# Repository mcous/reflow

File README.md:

# reflow

Heater controller with thermocouple feedback to control any AC heating appliance. It was originally developed to turn a toaster oven into a solder reflow oven, but it'll control anything that runs on AC and gets hot.

## hardware v0.1

The current board contains an AVR ATMega328P microcontroller, a Sharp S212S01 solid-state relay, and an Analog Devices AD8495 K-type thermocouple amplifier. It has a temperature precision of about 0.5 degrees C and is accurate to about +/- 2 degrees C. It also has start, stop, and mode buttons; a rotary encoder for temperature settings; and a four-digit seven-segment display for showing temperature in C or F. 

The schematic and PCB layout files were created in [KiCad](http://www.kicad-pcb.org) and live the in `pcb` directory.

## firmware v0.1.1

The current firmware has two basic modes: hit and hold. Hit mode takes the temperature up to the set point and then shuts off, while hold mode attempts to hold the temperature at the set-point by turning the heat on when the temperature is below the set point, and off when it's above. This is not PID. It can also display the temperature in either Celsius or Fahrenheit.

The firmware is written in C++ and compiled on OS X using the latest [CrossPack for AVR](http://www.obdev.at/products/crosspack/index.html) and lives in the `firmware` directory. It'll probably compile fine on Linux; no idea about Windows, though.

## operation

* To switch temperature units, hold the set wheel down (it's also a button) until you see an F after the temperature (Fahrenheit) or a number with a decimal point (Celsius)
* To switch modes between hit and hold, press and release the set wheel button; the display will show either "hit" or "hold" for whatever mode has been selected
* To select a set point, turn the set wheel until the display shows your desired temperature
* Press the start button to start heating; the red light will go out and the green light will illuminate
	* In hit mode, once the temperature is hit, the heating will stop and the green light will go out, replaced by the red light
	* In hold mode, the program will not stop unless you tell it to
* Press the stop button to stop heating; the green light will go out and the red light will illuminate
* Whenever the relay is closed (i.e. heat is on) the red LED labeled "HOT" will illuminate

## things this board has been used for

* reflow toaster oven (in hit mode)
* sous vide slow-cooker (in hold mode)

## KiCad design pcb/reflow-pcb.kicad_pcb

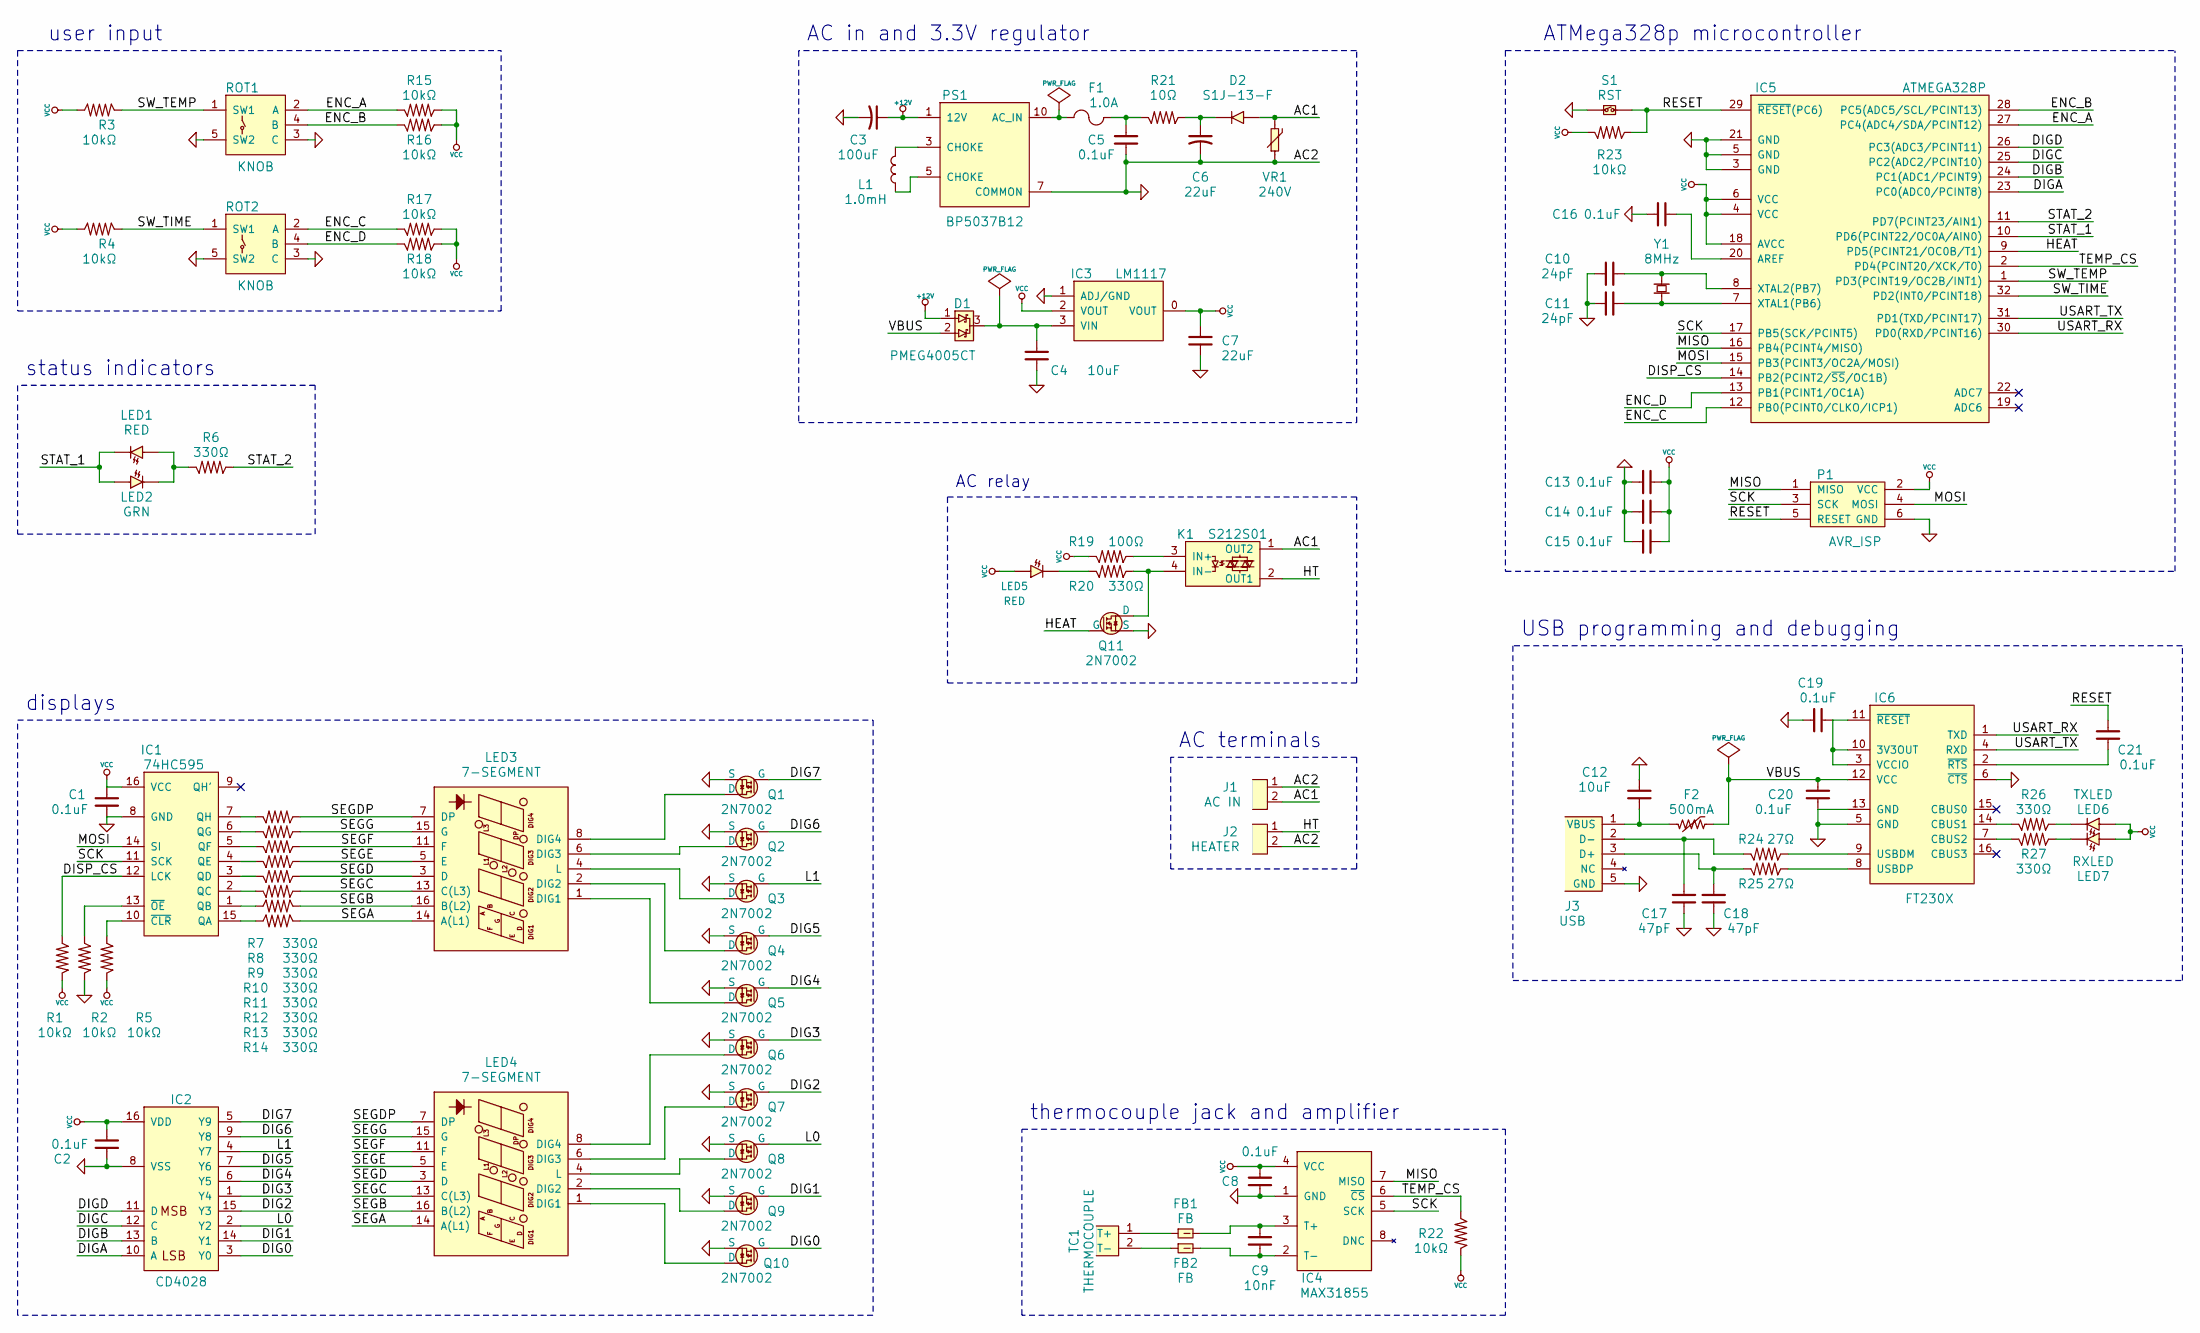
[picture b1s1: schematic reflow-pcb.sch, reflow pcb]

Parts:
C1, C2, C21: 0.1uF
C3: 100uF; Manuf. Part EEE-FT1E101AP
C4: 10uF
C5: 0.1uF; Manuf. Part CL31B104KEHSFNE
C6: 22uF; Manuf. Part EEU-EE2E220
C7: 22uF
C8, C13, C14, C15, C19, C20: 0.1uF; 0603(1608m)
C9: 10nF; 0603(1608m)
C10, C11: 24pF
C12: 10uF
C16: 0.1uF
C17, C18: 47pF; 0603(1608m)
D1: PMEG4005CT
D2: S1J-13-F; Manuf. Part S1J-13-F
F1: 1.0A; Manuf. Part C1Q 1
F2: 500mA; 1206(3216m); Part 0ZCJ0050FF2G
FB1, FB2: FB
IC1: 74HC595
IC2: CD4028
IC3: LM1117; Part AZ1117CH-3.3TRG1
IC4: MAX31855; Part MAX31855KASA+
IC5: ATMEGA328P; TQFP32_7mm; Part ATMEGA328P-AU
IC6: FT230X; SSOP16; Part FT230XS-R
J1: AC IN
J2: HEATER; 2-PIN_SCREW-TERM_P200MIL; Part OSTTC022162
J3: USB; MICROUSB_sm; Part 10118192-0001LF
K1: S212S01; SHARP_SIP_SSR; Part S212S01F
L1: 1.0mH; Manuf. Part SRR1260-102K
LED1, LED5: RED; LED-5mm
LED2: GRN; LED-5mm
LED3, LED4: 7-SEGMENT; Manuf. Part LTC-4727JR
LED6: TXLED; 0603(1608m)_led
LED7: RXLED; 0603(1608m)_led
P1: AVR_ISP; 2x3-array
PS1: BP5037B12; Manuf. Part BP5037B12
Q1, Q2, Q3, Q4, Q5, Q6, Q7, Q8, Q9, Q10, Q11: 2N7002; Manuf. Part 2N7002P,215
R1, R22, R23: 10kΩ
R2, R5: 10kΩ
R3, R4, R15, R16, R17, R18: 10kΩ; 0603(1608m)
R6: 330Ω
R7, R8, R9, R10, R11, R12, R13, R14, R20, R26, R27: 330Ω; 0603(1608m)
R19: 100Ω; 0603(1608m)
R21: 10Ω; Manuf. Part RC1206FR-0710RL
R24, R25: 27Ω; 0603(1608m)
ROT1, ROT2: KNOB; SF_ROTARY-ENCODER; Part RE130F-41-175F-12P
S1: RST
TC1: THERMOCOUPLE; THERMOCOUPLE_MINI_PCC-SMP; Part PCC-SMP-K
VR1: 240V; Manuf. Part MOV-14D241K
Y1: 8MHz

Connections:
+12V: C3.1, D1.1 (A1), PS1.1 (12V)
/AC1: D2.2 (A), J1.2, K1.1 (OUT2), VR1.2
/DIG0: IC2.3 (Y0), Q10.1 (G)
/DIG1: IC2.14 (Y1), Q9.1 (G)
/DIG2: IC2.15 (Y3), Q7.1 (G)
/DIG3: IC2.1 (Y4), Q6.1 (G)
/DIG4: IC2.6 (Y5), Q5.1 (G)
/DIG5: IC2.7 (Y6), Q4.1 (G)
/DIG6: IC2.9 (Y8), Q2.1 (G)
/DIG7: IC2.5 (Y9), Q1.1 (G)
/DIGA: IC2.10 (A), IC5.23 (PC0(ADC0/PCINT8))
/DIGB: IC2.13 (B), IC5.24 (PC1(ADC1/PCINT9))
/DIGC: IC2.12 (C), IC5.25 (PC2(ADC2/PCINT10))
/DIGD: IC2.11 (D), IC5.26 (PC3(ADC3/PCINT11))
/DISP_CS: IC1.12 (LCK), IC5.14 (PB2(PCINT2/~SS~/OC1B)), R1.2
/ENC_A: IC5.27 (PC4(ADC4/SDA/PCINT12)), R15.1, ROT1.2 (A)
/ENC_B: IC5.28 (PC5(ADC5/SCL/PCINT13)), R16.1, ROT1.4 (B)
/ENC_C: IC5.12 (PB0(PCINT0/CLKO/ICP1)), R17.1, ROT2.2 (A)
/ENC_D: IC5.13 (PB1(PCINT1/OC1A)), R18.1, ROT2.4 (B)
/HEAT: IC5.9 (PD5(PCINT21/OC0B/T1)), Q11.1 (G)
/HT: J2.1, K1.2 (OUT1)
/L0: IC2.2 (Y2), Q8.1 (G)
/L1: IC2.4 (Y7), Q3.1 (G)
/MISO: IC4.7 (MISO), IC5.16 (PB4(PCINT4/MISO)), P1.1 (MISO)
/MOSI: IC1.14 (SI), IC5.15 (PB3(PCINT3/OC2A/MOSI)), P1.4 (MOSI)
/RESET: C21.2, IC5.29 (~RESET~(PC6)), P1.5 (RESET), R23.2, S1.2
/SCK: IC1.11 (SCK), IC4.5 (SCK), IC5.17 (PB5(SCK/PCINT5)), P1.3 (SCK)
/SEGA: LED3.14 (A(L1)), LED4.14 (A(L1)), R14.1
/SEGB: LED3.16 (B(L2)), LED4.16 (B(L2)), R13.1
/SEGC: LED3.13 (C(L3)), LED4.13 (C(L3)), R12.1
/SEGD: LED3.3 (D), LED4.3 (D), R11.1
/SEGDP: LED3.7 (DP), LED4.7 (DP), R7.1
/SEGE: LED3.5 (E), LED4.5 (E), R10.1
/SEGF: LED3.11 (F), LED4.11 (F), R9.1
/SEGG: LED3.15 (G), LED4.15 (G), R8.1
/STAT_1: IC5.10 (PD6(PCINT22/OC0A/AIN0)), LED1.1 (C), LED2.2 (A)
/STAT_2: IC5.11 (PD7(PCINT23/AIN1)), R6.2
/SW_TEMP: IC5.1 (PD3(PCINT19/OC2B/INT1)), R3.1, ROT1.1 (SW1)
/SW_TIME: IC5.32 (PD2(INT0/PCINT18)), R4.1, ROT2.1 (SW1)
/TEMP_CS: IC4.6 (~CS~), IC5.2 (PD4(PCINT20/XCK/T0)), R22.2
/USART_RX: IC5.30 (PD0(RXD/PCINT16)), IC6.1 (TXD)
/USART_TX: IC5.31 (PD1(TXD/PCINT17)), IC6.4 (RXD)
/VBUS: C20.2, D1.2 (A2), F2.1, IC6.12 (VCC)
GND: C1.1, C2.2, C3.2, C4.1, C5.1, C6.2, C7.1, C8.1, C10.1, C11.1, C12.1, C13.1, C14.1, C15.1, C16.1, C17.1, C18.1, C19.1, C20.1, IC1.8 (GND), IC2.8 (VSS), IC3.1 (ADJ/GND), IC4.1 (GND), IC5.3 (GND), IC5.5 (GND), IC5.21 (GND), IC6.5 (GND), IC6.6 (~CTS~), IC6.13 (GND), J1.1, J2.2, J3.5 (GND), P1.6 (GND), PS1.7 (COMMON), Q1.2 (S), Q2.2 (S), Q3.2 (S), Q4.2 (S), Q5.2 (S), Q6.2 (S), Q7.2 (S), Q8.2 (S), Q9.2 (S), Q10.2 (S), Q11.2 (S), R2.1, ROT1.3 (C), ROT1.5 (SW2), ROT2.3 (C), ROT2.5 (SW2), S1.1, VR1.1
unnamed: C4.2, D1.3 (CC), IC3.3 (VIN)
unnamed: C5.2, F1.2, R21.1
unnamed: C6.1, D2.1 (C), R21.2
unnamed: C9.1, FB2.2, IC4.2 (T-)
unnamed: C9.2, FB1.2, IC4.3 (T+)
unnamed: C10.2, IC5.8 (XTAL2(PB7)), Y1.2
unnamed: C11.2, IC5.7 (XTAL1(PB6)), Y1.1
unnamed: C12.2, F2.2, J3.1 (VBUS)
unnamed: C16.2, IC5.20 (AREF)
unnamed: C17.2, J3.2 (D-), R24.1
unnamed: C18.2, J3.3 (D+), R25.1
unnamed: C19.2, IC6.3 (VCCIO), IC6.10 (3V3OUT), IC6.11 (~RESET~)
unnamed: C21.1, IC6.2 (~RTS~)
unnamed: F1.1, PS1.10 (AC_IN)
unnamed: FB1.1, TC1.1 (T+)
unnamed: FB2.1, TC1.2 (T-)
unnamed: IC1.1 (QB), R13.2
unnamed: IC1.2 (QC), R12.2
unnamed: IC1.3 (QD), R11.2
unnamed: IC1.4 (QE), R10.2
unnamed: IC1.5 (QF), R9.2
unnamed: IC1.6 (QG), R8.2
unnamed: IC1.7 (QH), R7.2
unnamed: IC1.10 (~CLR~), R5.2
unnamed: IC1.13 (~OE~), R2.2
unnamed: IC1.15 (QA), R14.2
unnamed: IC6.7 (CBUS2), R27.1
unnamed: IC6.8 (USBDP), R25.2
unnamed: IC6.9 (USBDM), R24.2
unnamed: IC6.14 (CBUS1), R26.1
unnamed: K1.3 (IN+), R19.2
unnamed: K1.4 (IN-), Q11.3 (D), R20.2
unnamed: L1.1, PS1.5 (CHOKE)
unnamed: L1.2, PS1.3 (CHOKE)
unnamed: LED1.2 (A), LED2.1 (C), R6.1
unnamed: LED3.1 (DIG1), Q5.3 (D)
unnamed: LED3.2 (DIG2), Q4.3 (D)
unnamed: LED3.4 (L), Q3.3 (D)
unnamed: LED3.6 (DIG3), Q2.3 (D)
unnamed: LED3.8 (DIG4), Q1.3 (D)
unnamed: LED4.1 (DIG1), Q10.3 (D)
unnamed: LED4.2 (DIG2), Q9.3 (D)
unnamed: LED4.4 (L), Q8.3 (D)
unnamed: LED4.6 (DIG3), Q7.3 (D)
unnamed: LED4.8 (DIG4), Q6.3 (D)
unnamed: LED5.1 (C), R20.1
unnamed: LED6.1 (C), R26.2
unnamed: LED7.1 (C), R27.2
VCC: C1.2, C2.1, C7.2, C8.2, C13.2, C14.2, C15.2, IC1.16 (VCC), IC2.16 (VDD), IC3.0 (VOUT), IC3.2 (VOUT), IC4.4 (VCC), IC5.4 (VCC), IC5.6 (VCC), IC5.18 (AVCC), LED5.2 (A), LED6.2 (A), LED7.2 (A), P1.2 (VCC), R1.1, R3.2, R4.2, R5.1, R15.2, R16.2, R17.2, R18.2, R19.1, R22.1, R23.1

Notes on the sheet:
status indicators
user input
displays
AC relay
thermocouple jack and amplifier
USB programming and debugging
ATMega328p microcontroller
AC terminals
AC in and 3.3V regulator

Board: 2 copper layers, 91 parts (1 on the bottom side), 93 nets, no tracks yet.

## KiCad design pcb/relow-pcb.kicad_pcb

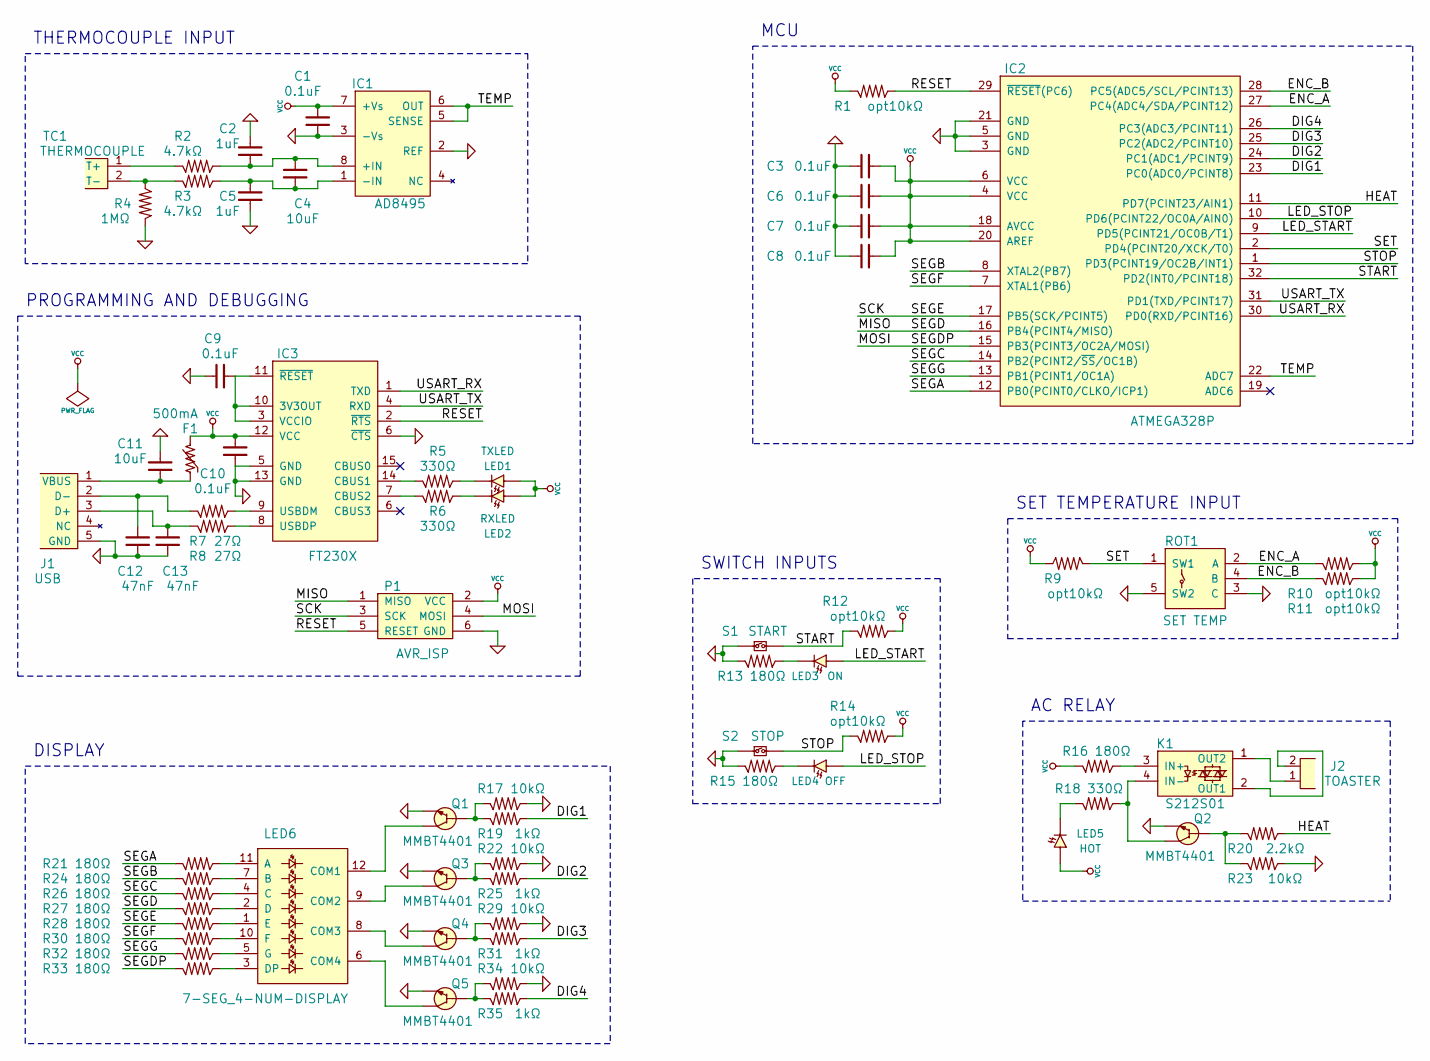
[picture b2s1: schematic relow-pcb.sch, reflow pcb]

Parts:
C1, C3, C6, C7, C8, C9, C10: 0.1uF; 0603(1608m)
C2, C5: 1uF; 0603(1608m)
C4, C11: 10uF; 0603(1608m)
C12, C13: 47nF; 0603(1608m)
F1: 500mA; 1206(3216m); Part 0ZCJ0050FF2G
IC1: AD8495; MSOP8; Part AD8495ARMZ
IC2: ATMEGA328P; TQFP32_7mm; Part ATMEGA328P-AU
IC3: FT230X; SSOP16; Part FT230XS-R
J1: USB; MICROUSB_sm; Part 10118192-0001LF
J2: TOASTER; 2-PIN_SCREW-TERM_P200MIL; Part OSTTC022162
K1: S212S01; SHARP_SIP_SSR; Part S212S01F
LED1: TXLED; 0603(1608m)_led
LED2: RXLED; 0603(1608m)_led
LED3: ON; LED-5mm
LED4: OFF; LED-5mm
LED5: HOT; LED-5mm
LED6: 7-SEG_4-NUM-DISPLAY; SF_4-DIGIT_7-SEGMENT_CC; Part COM-11405
P1: AVR_ISP; 2x3-array
Q1, Q2, Q3, Q4, Q5: MMBT4401; SOT23; Part MMBT4401LT1G
R1, R9, R10, R11, R12, R14: opt10kΩ; 0603(1608m)
R2, R3: 4.7kΩ; 0603(1608m)
R4: 1MΩ; 0603(1608m)
R5, R6, R18: 330Ω; 0603(1608m)
R7, R8: 27Ω; 0603(1608m)
R13, R15, R16, R21, R24, R26, R27, R28, R30, R32, R33: 180Ω; 0603(1608m)
R17, R22, R23, R29, R34: 10kΩ; 0603(1608m)
R19, R25, R31, R35: 1kΩ; 0603(1608m)
R20: 2.2kΩ; 0603(1608m)
ROT1: SET TEMP; SF_ROTARY-ENCODER; Part RE130F-41-175F-12P
S1: START; SPST_4-pin-thru
S2: STOP; SPST_4-pin-thru
TC1: THERMOCOUPLE; THERMOCOUPLE_MINI_PCC-SMP; Part PCC-SMP-K

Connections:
/DIG1: IC2.23 (PC0(ADC0/PCINT8)), R19.2
/DIG2: IC2.24 (PC1(ADC1/PCINT9)), R25.2
/DIG3: IC2.25 (PC2(ADC2/PCINT10)), R31.2
/DIG4: IC2.26 (PC3(ADC3/PCINT11)), R35.2
/ENC_A: IC2.27 (PC4(ADC4/SDA/PCINT12)), R10.1, ROT1.2 (A)
/ENC_B: IC2.28 (PC5(ADC5/SCL/PCINT13)), R11.1, ROT1.4 (B)
/HEAT: IC2.11 (PD7(PCINT23/AIN1)), R20.2
/LED_START: IC2.9 (PD5(PCINT21/OC0B/T1)), LED3.2 (A)
/LED_STOP: IC2.10 (PD6(PCINT22/OC0A/AIN0)), LED4.2 (A)
/MISO: IC2.16 (PB4(PCINT4/MISO)), P1.1 (MISO), R27.1
/MOSI: IC2.15 (PB3(PCINT3/OC2A/MOSI)), P1.4 (MOSI), R33.1
/RESET: IC2.29 (~RESET~(PC6)), IC3.2 (~RTS~), P1.5 (RESET), R1.2
/SCK: IC2.17 (PB5(SCK/PCINT5)), P1.3 (SCK), R28.1
/SEGA: IC2.12 (PB0(PCINT0/CLKO/ICP1)), R21.1
/SEGB: IC2.8 (XTAL2(PB7)), R24.1
/SEGC: IC2.14 (PB2(PCINT2/~SS~/OC1B)), R26.1
/SEGF: IC2.7 (XTAL1(PB6)), R30.1
/SEGG: IC2.13 (PB1(PCINT1/OC1A)), R32.1
/SET: IC2.2 (PD4(PCINT20/XCK/T0)), R9.1, ROT1.1 (SW1)
/START: IC2.32 (PD2(INT0/PCINT18)), R12.1, S1.2
/STOP: IC2.1 (PD3(PCINT19/OC2B/INT1)), R14.1, S2.2
/TEMP: IC1.5 (SENSE), IC1.6 (OUT), IC2.22 (ADC7)
/USART_RX: IC2.30 (PD0(RXD/PCINT16)), IC3.1 (TXD)
/USART_TX: IC2.31 (PD1(TXD/PCINT17)), IC3.4 (RXD)
GND: C1.1, C2.2, C3.1, C5.1, C6.1, C7.1, C8.1, C9.1, C10.1, C11.2, C12.1, C13.1, IC1.2 (REF), IC1.3 (-Vs), IC2.3 (GND), IC2.5 (GND), IC2.21 (GND), IC3.5 (GND), IC3.6 (CBUS3), IC3.13 (GND), J1.5 (GND), P1.6 (GND), Q1.2 (E), Q2.2 (E), Q3.2 (E), Q4.2 (E), Q5.2 (E), R4.1, R13.1, R15.1, R17.2, R22.2, R23.2, R29.2, R34.2, ROT1.3 (C), ROT1.5 (SW2), S1.1, S2.1; also elsewhere on the board
unnamed: LED6.11 (A), R21.2
unnamed: LED3.1 (C), R13.2
unnamed: LED4.1 (C), R15.2
unnamed: LED6.7 (B), R24.2
unnamed: LED6.4 (C), R26.2
unnamed: LED6.2 (D), R27.2
unnamed: LED6.1 (E), R28.2
unnamed: LED6.10 (F), R30.2
unnamed: LED6.5 (G), R32.2
unnamed: LED6.3 (DP), R33.2
unnamed: Q1.1 (B), R17.1, R19.1
unnamed: K1.3 (IN+), R16.2
unnamed: Q4.1 (B), R29.1, R31.1
unnamed: Q5.1 (B), R34.1, R35.1
unnamed: LED6.12 (COM1), Q1.3 (C)
unnamed: LED6.9 (COM2), Q3.3 (C)
unnamed: Q3.1 (B), R22.1, R25.1
unnamed: IC3.14 (CBUS1), R5.1
unnamed: IC3.7 (CBUS2), R6.1
unnamed: LED2.1 (C), R6.2
unnamed: IC3.8 (USBDP), R8.2
unnamed: C13.2, J1.3 (D+), R8.1
unnamed: LED1.1 (C), R5.2
unnamed: R2.1, TC1.1 (T+)
unnamed: K1.4 (IN-), Q2.3 (C), R18.2
unnamed: IC3.9 (USBDM), R7.2
unnamed: C9.2, IC3.3 (VCCIO), IC3.10 (3V3OUT), IC3.11 (~RESET~)
unnamed: J2.2, K1.2 (OUT1)
unnamed: LED5.1 (C), R18.1
unnamed: J2.1, K1.1 (OUT2)
unnamed: C12.2, J1.2 (D-), R7.1
unnamed: Q2.1 (B), R20.1, R23.1
unnamed: LED6.8 (COM3), Q4.3 (C)
unnamed: LED6.6 (COM4), Q5.3 (C)
unnamed: C2.1, C4.2, IC1.8 (+IN), R2.2
unnamed: R3.1, R4.2, TC1.2 (T-)
unnamed: C4.1, C5.2, IC1.1 (-IN), R3.2
unnamed: C11.1, F1.1, J1.1 (VBUS)
VCC: C1.2, C3.2, C6.2, C7.2, C8.2, C10.2, F1.2, IC1.7 (+Vs), IC2.4 (VCC), IC2.6 (VCC), IC2.18 (AVCC), IC2.20 (AREF), IC3.12 (VCC), LED1.2 (A), LED2.2 (A), LED5.2 (A), P1.2 (VCC), R1.1, R9.2, R10.2, R11.2, R12.2, R14.2, R16.1

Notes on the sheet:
SWITCH INPUTS
SET TEMPERATURE INPUT
DISPLAY
AC RELAY
THERMOCOUPLE INPUT
PROGRAMMING AND DEBUGGING
MCU

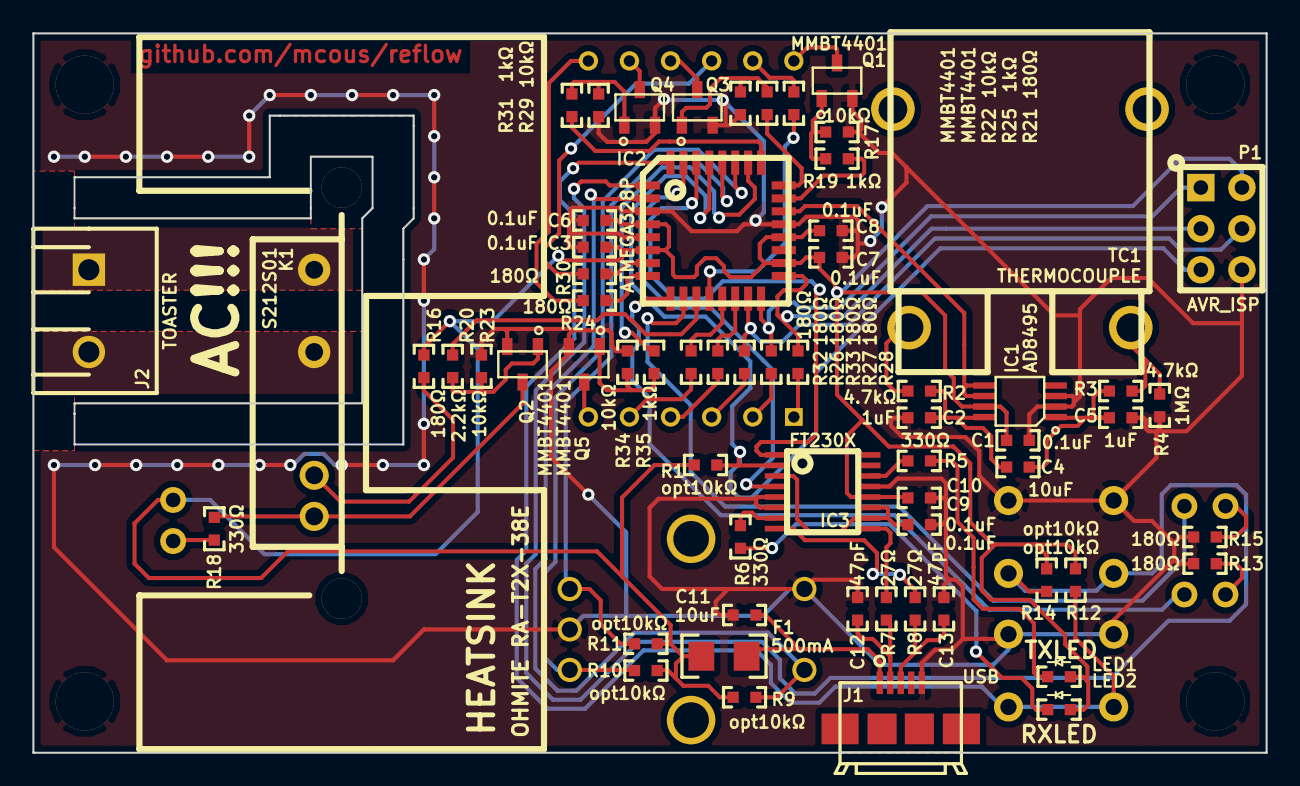
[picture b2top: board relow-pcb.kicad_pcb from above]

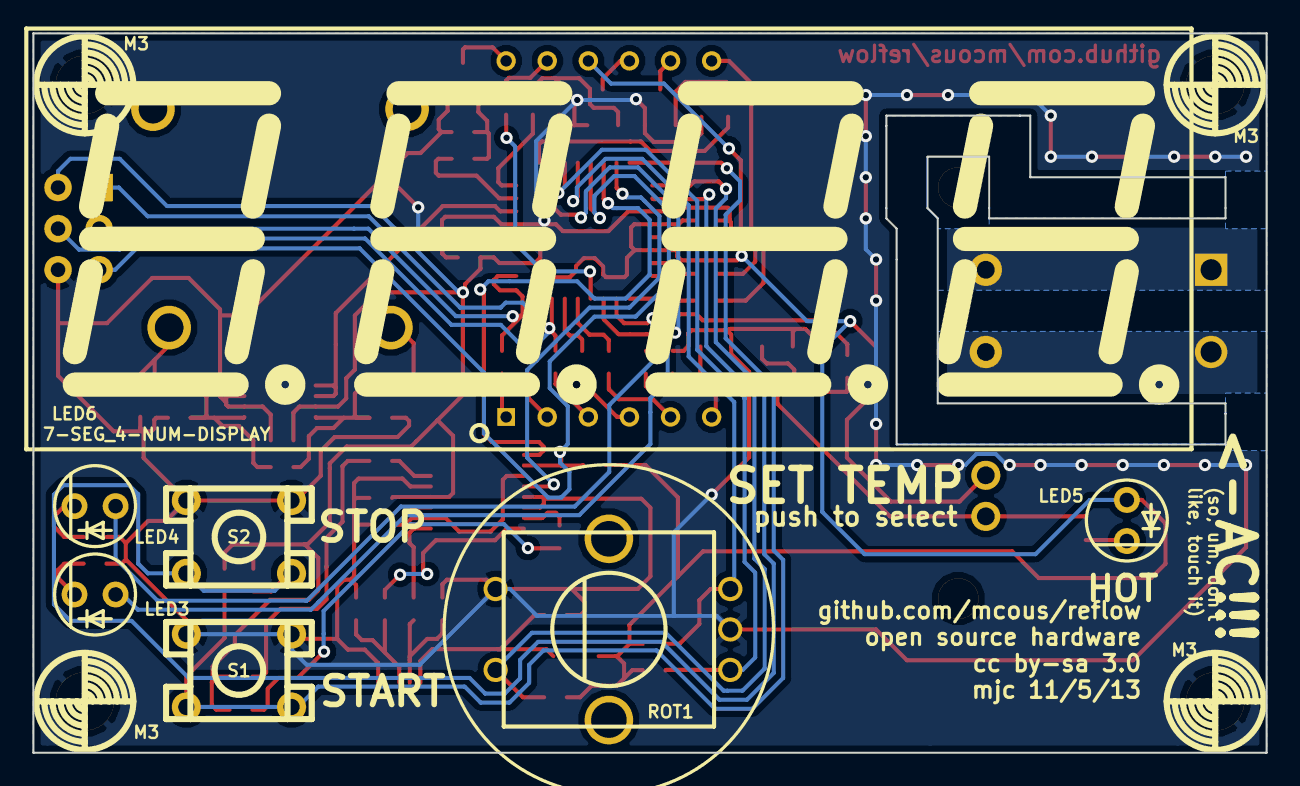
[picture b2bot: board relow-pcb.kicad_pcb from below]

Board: 2 copper layers, 76.2 x 44.5 mm, 75 parts (11 on the bottom side), 64 nets.

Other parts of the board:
M3, M3#2, M3#3, M3#4: VAL**; M3

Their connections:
GND: M3.1, M3#2.1, M3#3.1, M3#4.1; also elsewhere on the board

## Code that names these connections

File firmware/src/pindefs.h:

// reflow
// Copyright 2013 by Wiley Cousins, LLC.
// shared under the terms of the MIT License
//
// file: pindefs.h
// description: pin definitions file for the reflow oven controller

#ifndef REFLOW_PINDEFS_H
#define REFLOW_PINDEFS_H

// include for AVR register addresses and interrupt vectors
#include <avr/io.h>

// DDR and PIN from port register macros
#define DDR(port) (*(&port-1))
#define PIN(port) (*(&port-2))

// display ports
#define DISPLAY_DIG_PORT  PORTC
#define DISPLAY_DIG_MASK  0x0F
#define DISPLAY_SEG_PORT  PORTB
#define DISPLAY_SEG_MASK  0xFF
// display segment pins
#define DISPLAY_SEG_A   (1<<0)
#define DISPLAY_SEG_B   (1<<7)
#define DISPLAY_SEG_C   (1<<2)
#define DISPLAY_SEG_D   (1<<4)
#define DISPLAY_SEG_E   (1<<5)
#define DISPLAY_SEG_F   (1<<6)
#define DISPLAY_SEG_G   (1<<1)
#define DISPLAY_SEG_DP  (1<<3)

// pushbutton port
#define BUTTON_PORT   PORTD
#define BUTTON_SET    (1<<4)
#define BUTTON_START  (1<<2)
#define BUTTON_STOP   (1<<3)
#define BUTTON_MASK   ( BUTTON_STOP | BUTTON_START | BUTTON_SET )
// pushbutton polling / debounce timer
#define BUTTON_TIMER_OVF_vect  TIMER2_OVF_vect

// encoder port
#define ENCODER_PORT   PORTC
#define ENCODER_A      (1<<4)
#define ENCODER_B      (1<<5)
#define ENCODER_MASK   ( ENCODER_B | ENCODER_A )
#define ENCODER_SHIFT  4
// encoder pin change
#define ENCODER_PCIE        (1<<PCIE1)
#define ENCODER_PCMSK       PCMSK1
#define ENCODER_PCINT_vect  PCINT1_vect

// mode indicator LEDs
#define LED_PORT   PORTD
#define LED_STOP   (1<<6)
#define LED_START  (1<<5)
#define LED_MASK   (LED_START | LED_STOP)

// heater
#define HEAT_PORT  PORTD
#define HEAT_PIN   (1<<7)

// temperature reading
#define TEMP_ADC  (1<<7)

#endif

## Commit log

2013-11-02 got my towel
2013-11-02 starting kicad project
2013-11-02 starting schematic
2013-11-03 thermocouple circuit set up
2013-11-03 realy circuit done
2013-11-03 added rotary encoder
2013-11-03 going to bed
2013-11-03 added a display
2013-11-03 initial pass at schematic done
2013-11-04 I lied. Adding a FTDI USB to USART
2013-11-04 might actually be done with this schematic
2013-11-04 got some component assignement going on
2013-11-04 footprint assignment almost done. going to bed
2013-11-05 working on the board
2013-11-05 components placed. starting traces
2013-11-05 laying traces like it's my job
2013-11-05 layout done. ready to order (after triple checking)
2013-11-05 minor trace changes and gerbers plotted
2013-11-05 going to bed again
2013-11-05 USB caps should be 47pF, not 47nF
2013-11-05 how about i spell "reflow" correctly?
2013-11-05 adding schematic plot to rev control
2013-11-05 moving gerber files to gerber folder
2013-11-05 this version sent to fabrication
2013-11-20 adding Makefile
2013-11-21 can't get olimex isp to work, so switching to Arduino as ISP
2013-11-21 adding intial application files
2013-11-21 initial code fills 8-segment display
2013-11-21 adding display files
2013-11-21 pindefs file
2013-11-21 got a display that can display floats
2013-11-21 adding input class files
2013-11-21 button inputs are working
2013-11-21 renamed input class to buttons
2013-11-21 adding files for rotary encoder class
2013-11-21 oops, stayed up kinda late. thermocouple is working, as is a lot of the app
2013-11-21 ok actually going to bed
2014-01-02 this works well enough to toast boards
2014-01-20 adding FTDI RTS cap. fixes #2
2014-01-21 schematic first pass done. got that AC converter on board
2014-01-21 calling it a night
2014-01-30 schematic cleanup and component selection
2014-02-01 starting to move font to progmem
2014-02-02 makefile now generates a mapfile during linking
2014-02-04 redid the ADC to temperature math to be better
2014-02-04 changed buttons to polling only
2014-02-04 moved encoder lookup table to program memory
2014-02-05 font file is alledgedly in program space but i have my suspicions
2014-02-05 renaming avrdude test target in anticipation of unit tests
2014-02-05 adding a unit testing framework for non-hardware classes
2014-02-05 starting a new clas for the temperature
2014-02-05 got some tests going
2014-02-05 gitignore for test excecutables
2014-02-05 celcius class now saves temparature in a 4x scaled rep
2014-02-05 adding boolean operators
2014-02-05 celcius class now has boolean operators and compound assignment operators
2014-02-06 some stuff
2014-02-06 hey look I can't spell celsius
2014-02-06 all tests passing for celsius toStrings for C anf F
2014-02-06 safety commit
2014-02-06 main app now uses celsius class instead of floats for temperature
2014-02-08 working from my imac
2014-02-08 pure polling buttons work
2014-02-08 continuing display work
2014-02-08 progmem display seems to work
2014-02-08 display based on strings sorta working
2014-02-08 removing old comments
2014-02-09 fixed display ghosting
2014-02-09 trying to get open thermocouple detection working
2014-02-09 right justify temp display
2014-02-09 fixing bug with strings taking 4 dgits
2014-02-09 updated schematic plot
2014-02-10 basic events framework seems to operate fairly well
2014-02-10 working on improving adc
2014-02-11 added temp display in F, automatic display of target temp when encoder is turned, and oversampled the ADC to 11-bits of precision
2014-02-11 cleaning comments and includes
2014-02-11 improved encoder responsiveness and speed
2014-02-11 now has different modes for hit temp and hold temp
2014-02-12 updating celsius test to match new fahrenheit toString
2014-02-12 added a char to the fahrenheit string tester
2014-02-24 updating readme
2014-03-06 some schematic work.
2014-03-14 updating readme for correctness, grammar
2014-06-04 preparing for new layout
2014-06-05 work on layout
2014-06-05 work on dimensions

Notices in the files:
pcb/reflow-pcb.kicad_pcb:
shared under the terms of the Creative Commons Attribution Share-Alike 3.0 license
pcb/reflow-pcb.sch:
copyright 2014 by Wiley Cousins
shared under the terms of the Creative Commons Attribution Share-Alike 4.0 license
pcb/relow-pcb.kicad_pcb:
cc by-sa 3.0
